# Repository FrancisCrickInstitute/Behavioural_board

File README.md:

# Behavioural_board

This piece of hardware is a Teensy 3.2, Teensy LC or Teensy 4 [1] breakout board with 4 valve controls and (capacitive) licking sensors and with the same amount of digital inputs/outputs (8 in total). This device pretends to be a tool for behavioural experiments which need to control up to four valves and sense 4 licking sensors. The board has eight digital pins with interrupt capability. These pins are connected to a BNC and they can be used to display digital signals or to trigger externally the valves for instance. The Teensy 3.2 performs very well on the capacitive sensor library [2] achieving sub-millisecond sampling periods while using one licking sensor at 120 MHz clock speed. All thought the licking frequency in mice is ~7 Hz, sub-millisecond resolution is required when accurate sensing of lick onset and offset is desired [3]. There is also an Incremental encoder connection for 5V Encoders with logic level shifters for phases A and B.

# R1-R8 resistor values (Capacitive sensor pins resistors)
The value of the capacitive sensor emitter is 1MΩ and the receiver digital pin has a 1kΩ resistance value to avoid an accidental electric shock [5]. The value of the high resistance value resistor can be changed to higher values in order to increase sensitivity.

# R9-R12 Calculation example (Transistor base current)
The solenoid valve used for the design is the Lee company model LHDA0533215H. The current needed on the transistor collector has been calculated using the power and the resistance from the manufacturer specifications [4]. Different solenoid valves may require changing the transistor base resistor. More details on "R9-R12 Calculation example (Transistor base).pdf"

# Limitations

If you are using Teensy LC Pin 1 does not have interrupt capability, therefore Trigger 1 cannot be used using interrupts. The DAC BNC connector is wired with to A14 of Teensy 3.2  and A12 of LC so it cannot be used with the Teensy 4.0.

# References

[1] 	"https://www.pjrc.com/teensy/teensy31.html". 

[2] 	"https://github.com/PaulStoffregen/CapacitiveSensor". 

[3] 	B. Williams, A. Speed and B. Haider, "A novel device for real-time measurement and manipulation of licking behavior in head-fixed mice," Journal of Neurophisiology, vol. 120, pp. 2975-2987, 2018. 

[4] 	"https://www.theleeco.com/products/electro-fluidic-systems/solenoid-valves/control-valves/lhd-series/3-port/ported/". 

[5] 	"https://www.pjrc.com/teensy/td_libs_CapacitiveSensor.html".

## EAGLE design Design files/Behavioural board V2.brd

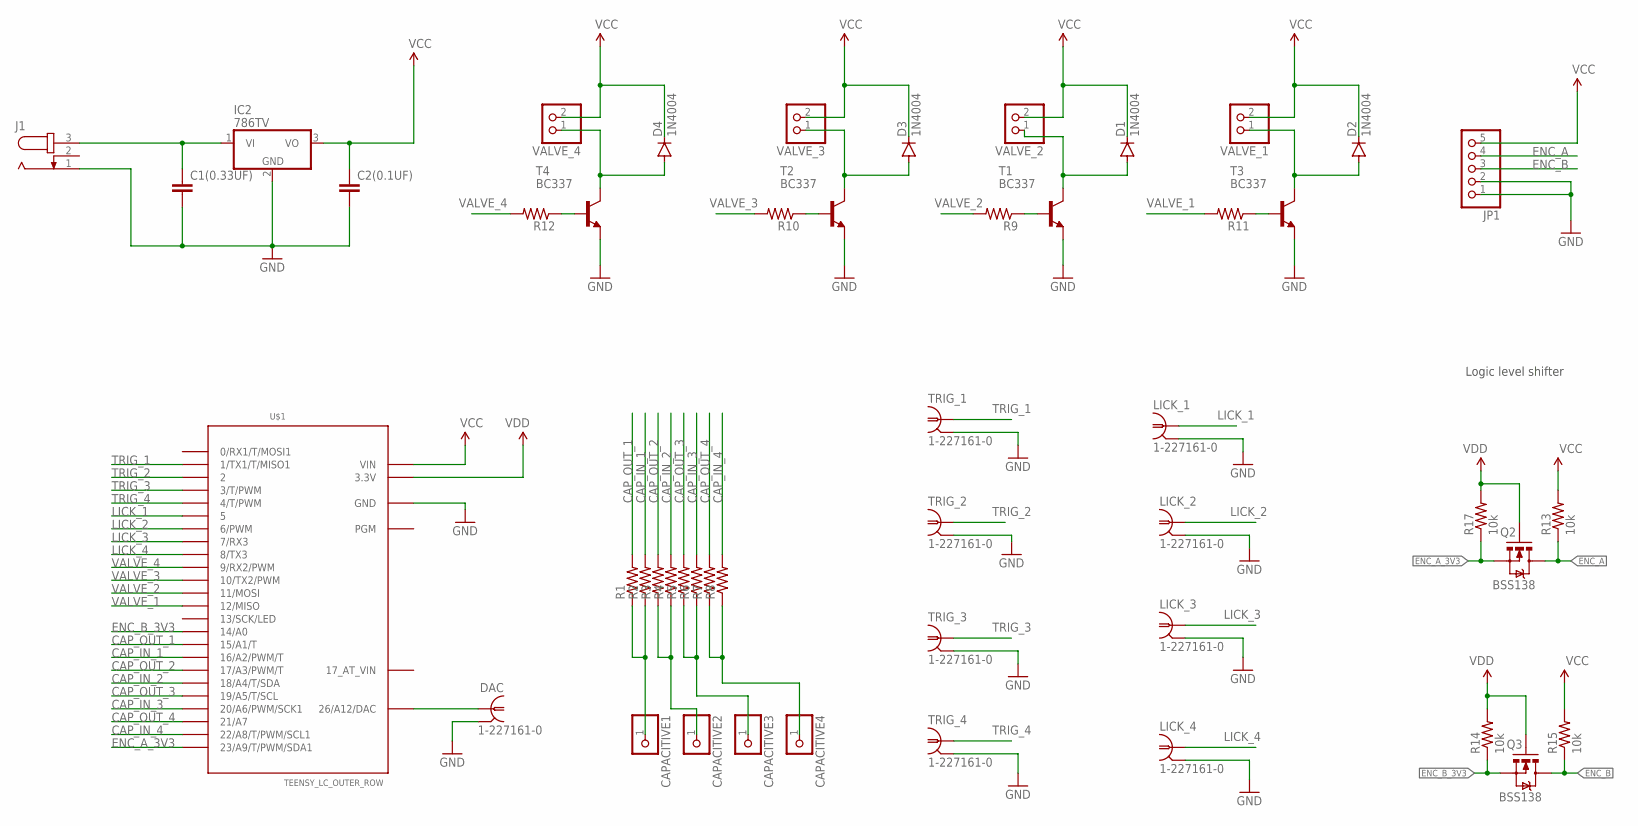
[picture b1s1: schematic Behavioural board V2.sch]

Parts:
C1(0.33UF): C2.5/4; C2.5-4
C2(0.1UF): C2.5/2; C2.5-2
CAPACITIVE1, CAPACITIVE2, CAPACITIVE3, CAPACITIVE4: PINHD-1X1; 1X01
D1, D2, D3, D4: 1N4004; DO41-10
DAC: 1-227161-0; AMP_227161
IC2: 786TV; TO220V
J1: JACK-PLUG0; SPC4077
JP1: PINHD-1X5; 1X05
LICK_1, LICK_2, LICK_3, LICK_4: 1-227161-0; AMP_227161
Q2, Q3: BSS138; SOT23-3
R1, R2, R3, R4, R5, R6, R7, R8, R9, R10, R11, R12: R-US_0207/10; 0207/10
R13, R14, R15, R17: 10k; 0207/10
T1, T2, T3, T4: BC337; TO92
TRIG_1, TRIG_2, TRIG_3, TRIG_4: 1-227161-0; AMP_227161
U$1: TEENSY_LC_OUTER_ROW; TEENSY_3.0-3.2&LC_OUTER_ROW
VALVE_1, VALVE_2, VALVE_3, VALVE_4: PINHD-1X2; 1X02

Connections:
12V: C1(0.33UF).1, IC2.1 (VI), J1.3
CAP_IN_1: R2.2, U$1.16/A2 (16/A2/PWM/T)
CAP_IN_2: R4.2, U$1.18/A4 (18/A4/T/SDA)
CAP_IN_3: R6.2, U$1.20/A6 (20/A6/PWM/SCK1)
CAP_IN_4: R8.2, U$1.22/A8 (22/A8/T/PWM/SCL1)
CAP_OUT_1: R1.2, U$1.15/A1 (15/A1/T)
CAP_OUT_2: R3.2, U$1.17/A3 (17/A3/PWM/T)
CAP_OUT_3: R5.2, U$1.19/A5 (19/A5/T/SCL)
CAP_OUT_4: R7.2, U$1.21/A7
ENC_A: JP1.4, Q2.3 (D), R13.1
ENC_A_3V3: Q2.2 (S), R17.1, U$1.23/A9 (23/A9/T/PWM/SDA1)
ENC_B: JP1.3, Q3.3 (D), R15.1
ENC_B_3V3: Q3.2 (S), R14.1, U$1.14/A0
GND: C1(0.33UF).2, C2(0.1UF).2, DAC.2, IC2.2 (GND), J1.1, JP1.1, JP1.2, LICK_1.2, LICK_2.2, LICK_3.2, LICK_4.2, T1.1 (E), T2.1 (E), T3.1 (E), T4.1 (E), TRIG_1.2, TRIG_2.2, TRIG_3.2, TRIG_4.2, U$1.AGND (GND), U$1.GND, U$1.GND1 (GND)
LICK_1: LICK_1.1, U$1.5
LICK_2: LICK_2.1, U$1.6 (6/PWM)
LICK_3: LICK_3.1, U$1.7 (7/RX3)
LICK_4: LICK_4.1, U$1.8 (8/TX3)
unnamed: DAC.1, U$1.RESET/DAC (26/A12/DAC)
unnamed: CAPACITIVE1.1, R1.1, R2.1
unnamed: CAPACITIVE2.1, R3.1, R4.1
unnamed: CAPACITIVE3.1, R5.1, R6.1
unnamed: CAPACITIVE4.1, R7.1, R8.1
unnamed: R11.1, T3.2 (B)
unnamed: D2.A, T3.3 (C), VALVE_1.1
unnamed: R9.1, T1.2 (B)
unnamed: D1.A, T1.3 (C), VALVE_2.1
unnamed: R10.1, T2.2 (B)
unnamed: D3.A, T2.3 (C), VALVE_3.1
unnamed: R12.1, T4.2 (B)
unnamed: D4.A, T4.3 (C), VALVE_4.1
TRIG_1: TRIG_1.1, U$1.1 (1/TX1/T/MISO1)
TRIG_2: TRIG_2.1, U$1.2
TRIG_3: TRIG_3.1, U$1.3 (3/T/PWM)
TRIG_4: TRIG_4.1, U$1.4 (4/T/PWM)
VALVE_1: R11.2, U$1.12 (12/MISO)
VALVE_2: R9.2, U$1.11 (11/MOSI)
VALVE_3: R10.2, U$1.10 (10/TX2/PWM)
VALVE_4: R12.2, U$1.9 (9/RX2/PWM)
VCC: C2(0.1UF).1, D1.C, D2.C, D3.C, D4.C, IC2.3 (VO), JP1.5, R13.2, R15.2, U$1.VIN, VALVE_1.2, VALVE_2.2, VALVE_3.2, VALVE_4.2
VDD: Q2.1 (G), Q3.1 (G), R14.2, R17.2, U$1.3.3V, U$1.3.3V1 (3.3V)

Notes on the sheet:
Logic level shifter

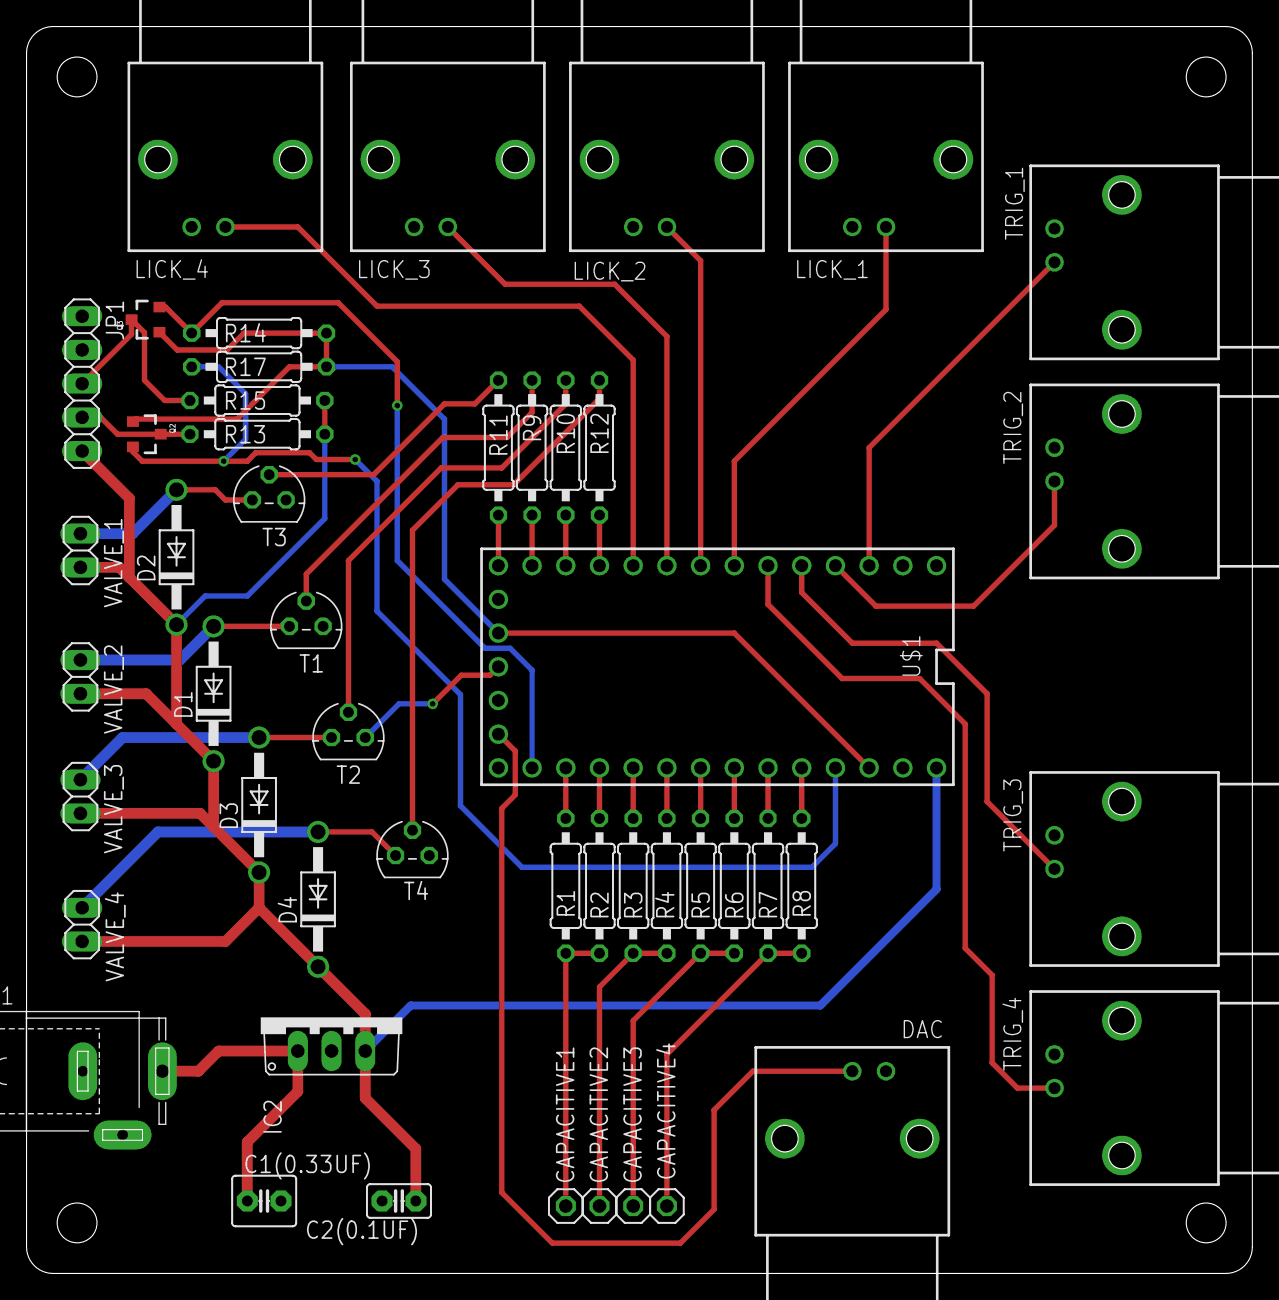
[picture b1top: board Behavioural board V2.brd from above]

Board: 2 copper layers, 92.4 x 94.0 mm, 49 parts (0 on the bottom side), 41 nets.

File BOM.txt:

Partlist exported from C:/Users/ferrerx/Documents/GitHub/Behavioural_board/Design files/Behavioural board V2.sch at 6/17/2022 1:58 PM

Qty Value               Device              Package                     Parts                                                               Description                            MF               MPN      OC_FARNELL OC_NEWARK POPULARITY SPICEPREFIX
1                       C2.5/2              C2.5-2                      C2(0.1UF)                                                           CAPACITOR                                                                             28                    
1                       C2.5/4              C2.5-4                      C1(0.33UF)                                                          CAPACITOR                                                                             6                     
1                       JACK-PLUG0          SPC4077                     J1                                                                  DC POWER JACK                                                    unknown    unknown   0                     
4                       PINHD-1X1           1X01                        CAPACITIVE1, CAPACITIVE2, CAPACITIVE3, CAPACITIVE4                  PIN HEADER                                                                            64                    
4                       PINHD-1X2           1X02                        VALVE_1, VALVE_2, VALVE_3, VALVE_4                                  PIN HEADER                                                                            98                    
1                       PINHD-1X5           1X05                        JP1                                                                 PIN HEADER                                                                            69                    
12                      R-US_0207/10        0207/10                     R1, R2, R3, R4, R5, R6, R7, R8, R9, R10, R11, R12                   RESISTOR, American symbol                                                             36         R          
9   1-227161-0          1-227161-0          AMP_227161                  DAC, LICK_1, LICK_2, LICK_3, LICK_4, TRIG_1, TRIG_2, TRIG_3, TRIG_4 JACK,  RIGHT ANGLE, 50 OHM, PCB, BNC   TYCO ELECTRONICS 1-227161 unknown    33B3200   0                     
4   10k                 R-US_0207/10        0207/10                     R13, R14, R15, R17                                                  RESISTOR, American symbol                                                             36         R          
4   1N4004              1N4004              DO41-10                     D1, D2, D3, D4                                                      DIODE                                                                                 82                    
1   786TV               786TV               TO220V                      IC2                                                                 Positive VOLTAGE REGULATOR                                                            0                     
4   BC337               BC337               TO92                        T1, T2, T3, T4                                                      NPN TRANSISTOR                                                                        2                     
2   BSS138              MOSFET-NCHANNELSMD  SOT23-3                     Q2, Q3                                                                                                                                                                          
1   TEENSY_LC_OUTER_ROW TEENSY_LC_OUTER_ROW TEENSY_3.0-3.2&LC_OUTER_ROW U$1                                                                 Teensy LC with only outer row of pins.

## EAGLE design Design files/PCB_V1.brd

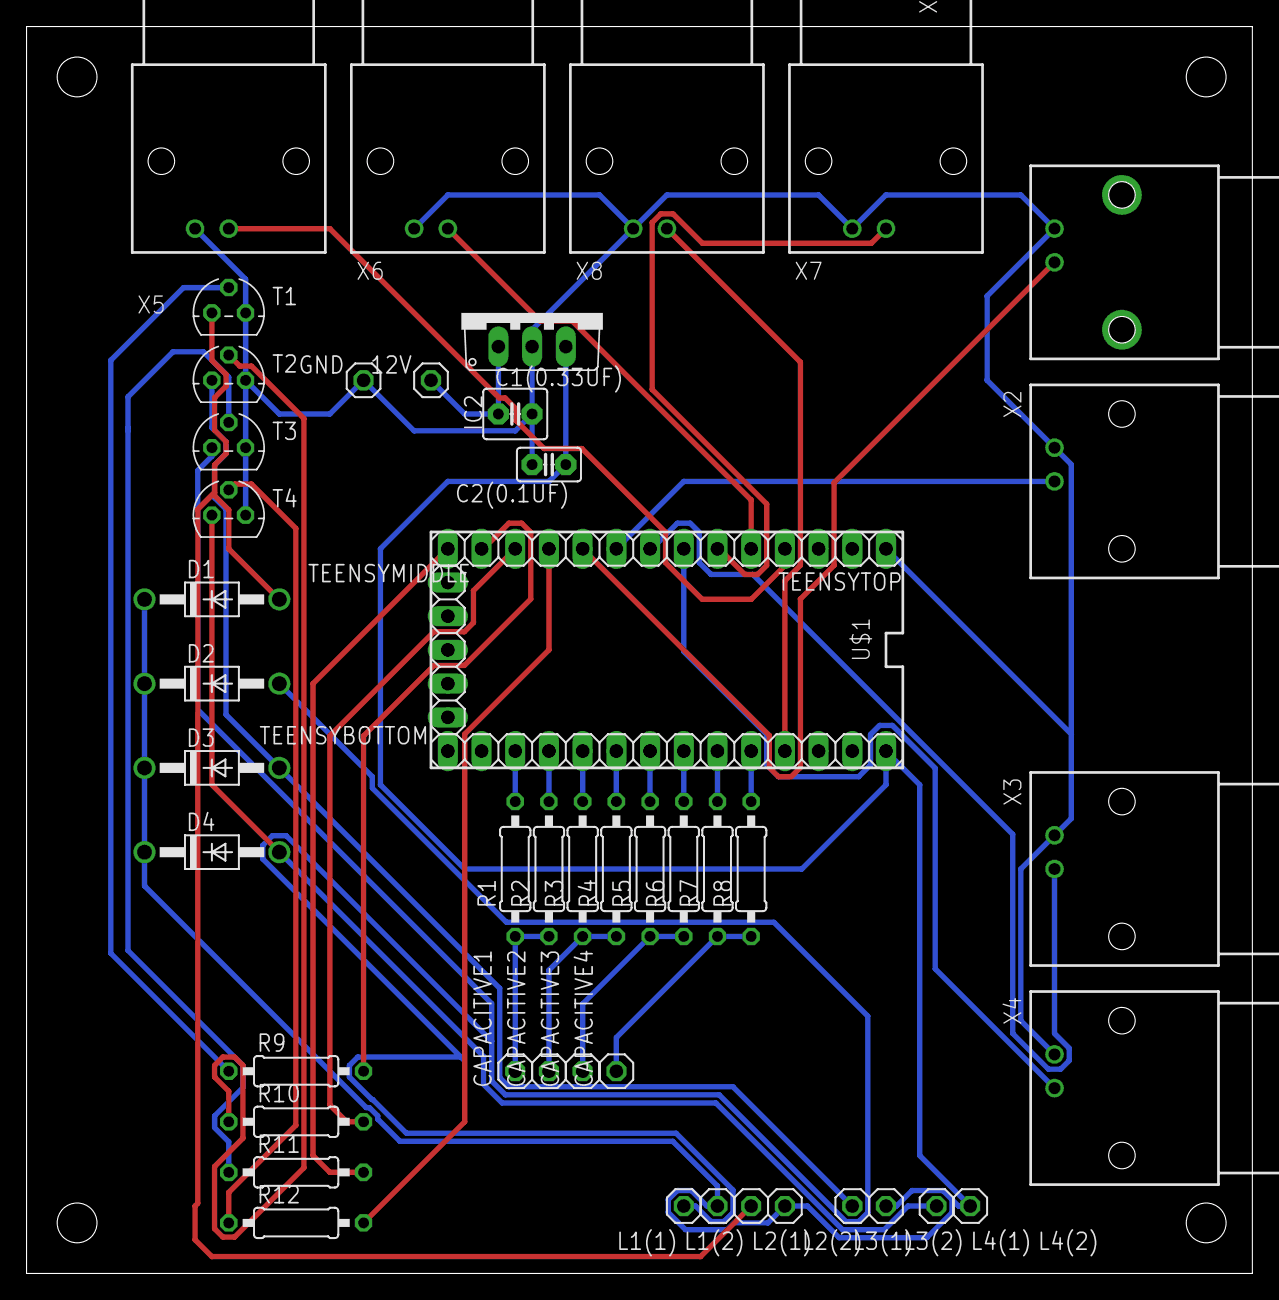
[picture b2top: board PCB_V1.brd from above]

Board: 2 copper layers, 92.4 x 94.0 mm, 49 parts (0 on the bottom side), 37 nets.

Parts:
12V: 1X01
C1(0.33UF): C2.5-4
C2(0.1UF): C2.5-2
CAPACITIVE1, CAPACITIVE2, CAPACITIVE3, CAPACITIVE4: 1X01
D1, D2, D3, D4: 1N4004; DO41-10
GND: 1X01
IC2: 786TV; TO220V
L1(1), L1(2), L2(1), L2(2), L3(1), L3(2), L4(1), L4(2): 1X01
R1, R2, R3, R4, R5, R6, R7, R8, R9, R10, R11, R12: 0207/10
T1, T2, T3, T4: BC337; TO92
TEENSYBOTTOM: 1X14
TEENSYMIDDLE: 1X05
TEENSYTOP: 1X14
U$1: TEENSY_LC_OUTER_ROW; TEENSY_3.0-3.2&LC_OUTER_ROW
X1, X2, X3, X4, X5, X6, X7, X8: 1-227161-0; AMP_227161

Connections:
3.3V: U$1.3.3V, U$1.3.3V1
5V: C2(0.1UF).1, D1.C, D2.C, D3.C, D4.C, IC2.3, L1(2).1, L2(2).1, L3(2).1, L4(2).1, TEENSYBOTTOM.14
GND: U$1.AGND, U$1.GND, U$1.GND1
unnamed: TEENSYTOP.10, X1.1
unnamed: TEENSYTOP.4, X5.1
unnamed: TEENSYTOP.9, X2.1
unnamed: 12V.1, C1(0.33UF).1, IC2.1
unnamed: TEENSYTOP.7, X4.1
unnamed: TEENSYTOP.8, X3.1
unnamed: R1.2, TEENSYBOTTOM.3
unnamed: TEENSYTOP.5, X6.1
unnamed: R2.2, TEENSYBOTTOM.4
unnamed: TEENSYTOP.6, X7.1
unnamed: R3.2, TEENSYBOTTOM.5
unnamed: R11.2, TEENSYTOP.14
unnamed: R4.2, TEENSYBOTTOM.6
unnamed: R5.2, TEENSYBOTTOM.7
unnamed: R6.2, TEENSYBOTTOM.8
unnamed: R7.2, TEENSYBOTTOM.9
unnamed: R8.2, TEENSYBOTTOM.10
unnamed: CAPACITIVE1.1, R1.1, R2.1
unnamed: CAPACITIVE2.1, R3.1, R4.1
unnamed: CAPACITIVE3.1, R5.1, R6.1
unnamed: CAPACITIVE4.1, R7.1, R8.1
unnamed: R11.1, T3.2
unnamed: D2.A, L1(1).1, T3.3
unnamed: TEENSYBOTTOM.11, X8.1
unnamed: R9.2, TEENSYTOP.13
unnamed: R9.1, T1.2
unnamed: D1.A, L2(1).1, T1.3
unnamed: R10.2, TEENSYTOP.12
unnamed: R10.1, T2.2
unnamed: D3.A, L3(1).1, T2.3
unnamed: R12.1, T4.2
unnamed: D4.A, L4(1).1, T4.3
unnamed: R12.2, TEENSYTOP.11
unnamed: C1(0.33UF).2, C2(0.1UF).2, GND.1, IC2.2, T1.1, T2.1, T3.1, T4.1, TEENSYTOP.1, X1.2, X2.2, X3.2, X4.2, X5.2, X6.2, X7.2, X8.2

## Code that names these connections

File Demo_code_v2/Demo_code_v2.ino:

#include <CapacitiveSensor.h>

byte N = 20;

//Capacitive sensor objects
CapacitiveSensor   CS_1 = CapacitiveSensor(15,16);
CapacitiveSensor   CS_2 = CapacitiveSensor(17,18);
CapacitiveSensor   CS_3 = CapacitiveSensor(19,20);
CapacitiveSensor   CS_4 = CapacitiveSensor(21,22);

// Licking sensor variables
long lick_1;
long lick_2;
long lick_3;
long lick_4;

//Valve variables
int valve_1 = 12;
int valve_2 = 11;
int valve_3 = 10;
int valve_4 = 9;

//Input/output pins

int trig_1 = 1; //IO_pin_1
int trig_2 = 2; //IO_pin_2
int trig_3 = 3; //IO_pin_3
int trig_4 = 4; //IO_pin_4
int lick_1_out = 5; //IO_pin_5
int lick_2_out = 6; //IO_pin_6
int lick_3_out = 7; //IO_pin_7
int lick_4_out = 8; //IO_pin_8

volatile bool state = LOW;
volatile bool state_2 = LOW;
volatile bool state_3 = LOW;
volatile bool state_4 = LOW;

elapsedMillis outputTimer = 0;

int th = 5000;

//Encoder encoder(23,14); // mistake connecting encoder to pin 13 (it has the LED attached)

void setup() 
{
  CS_1.set_CS_AutocaL_Millis(0xFFFFFFFF);
  CS_2.set_CS_AutocaL_Millis(0xFFFFFFFF);
  CS_3.set_CS_AutocaL_Millis(0xFFFFFFFF);
  CS_4.set_CS_AutocaL_Millis(0xFFFFFFFF);

  //Pins to be externally triggered
  //pinMode(trig_1, INPUT_PULLUP); // Teensy LC does not have interrupt capability on pin 1
  pinMode(trig_2, INPUT_PULLUP);
  pinMode(trig_3, INPUT_PULLUP);
  pinMode(trig_4, INPUT_PULLUP);
  
  //Interrupt routines can be used to externally trigger the valves for instance
  //attachInterrupt(digitalPinToInterrupt(trig_1),change, RISING); // Teensy LC does not have interrupt capability on pin 1
  attachInterrupt(digitalPinToInterrupt(trig_2),change_2, RISING);
  attachInterrupt(digitalPinToInterrupt(trig_3),change_3, RISING);
  attachInterrupt(digitalPinToInterrupt(trig_4),change_4, RISING);
  
  // Pins that can be used as a digital oputput
//  pinMode(trig_1, OUTPUT);
//  pinMode(trig_2, OUTPUT);
//  pinMode(trig_3, OUTPUT);
//  pinMode(trig_4, OUTPUT);

  //Valve pins declared as an output
  pinMode(lick_1_out, OUTPUT);
  pinMode(lick_2_out, OUTPUT);
  pinMode(lick_3_out, OUTPUT);
  pinMode(lick_4_out, OUTPUT);

  // Pins that can be used as a digital oputput
  digitalWrite(lick_1_out, LOW);
  digitalWrite(lick_2_out, LOW);
  digitalWrite(lick_3_out, LOW);
  digitalWrite(lick_4_out, LOW);

  //Valve pins declared as an output
  pinMode(valve_1, OUTPUT);
  pinMode(valve_2, OUTPUT);
  pinMode(valve_3, OUTPUT);
  pinMode(valve_4, OUTPUT);
}

void loop() 
{
  //Variable to check the performance of the loop function in us
  //long start = micros();

  //Read all the licking sensors
  lick_1 =  CS_1.capacitiveSensor(N);
  lick_2 =  CS_2.capacitiveSensor(N);
  lick_3 =  CS_3.capacitiveSensor(N);
  lick_4 =  CS_4.capacitiveSensor(N);

  // Actuate the valves, when each of the trig_ pins see a rising edge the state variable changes cand the 
  // vale state also changes
  //digitalWrite(valve_1,state);
  digitalWrite(valve_2,state_2);
  digitalWrite(valve_3,state_3);
  digitalWrite(valve_4,state_4);

  // Convert the licking signal to a digital output for a certain threshold
  if (lick_1 >= th)
    {
      digitalWrite(lick_1_out, HIGH);
    }
  else if (lick_1 < th)
    {
      digitalWrite(lick_1_out, LOW);
    }
    
  if (lick_2 >= th)
    {
      digitalWrite(lick_2_out, HIGH);
    }
  else if (lick_2 < th)
    {
      digitalWrite(lick_2_out, LOW);
    }
    
  if (lick_3 >= th)
    {
      digitalWrite(lick_3_out, HIGH);
    }
  else if (lick_3 < th)
    {
      digitalWrite(lick_3_out, LOW);
    }

  if (lick_4 >= th)
    {
      digitalWrite(lick_4_out, HIGH);
    }
  else if (lick_4 < th)
    {
      digitalWrite(lick_4_out, LOW);
    }

  
  // print position for display
  if (outputTimer > 20)  
  {
    outputTimer = 0;
    //Serial.println(state_4);
    //Serial.println(micros() - start);
  }
  

}

void change()
{
  state = !state;
}

void change_2()
{
  state_2 = !state_2;
}

void change_3()
{
  state_3 = !state_3;
}

void change_4()
{
  state_4 = !state_4;
}

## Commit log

2022-07-07 Readme V2

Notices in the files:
parts and their libraries:
SparkFun-Aesthetics: Licensing: CC v3.0 Share-Alike You are welcome to use this library for commercial purposes.
